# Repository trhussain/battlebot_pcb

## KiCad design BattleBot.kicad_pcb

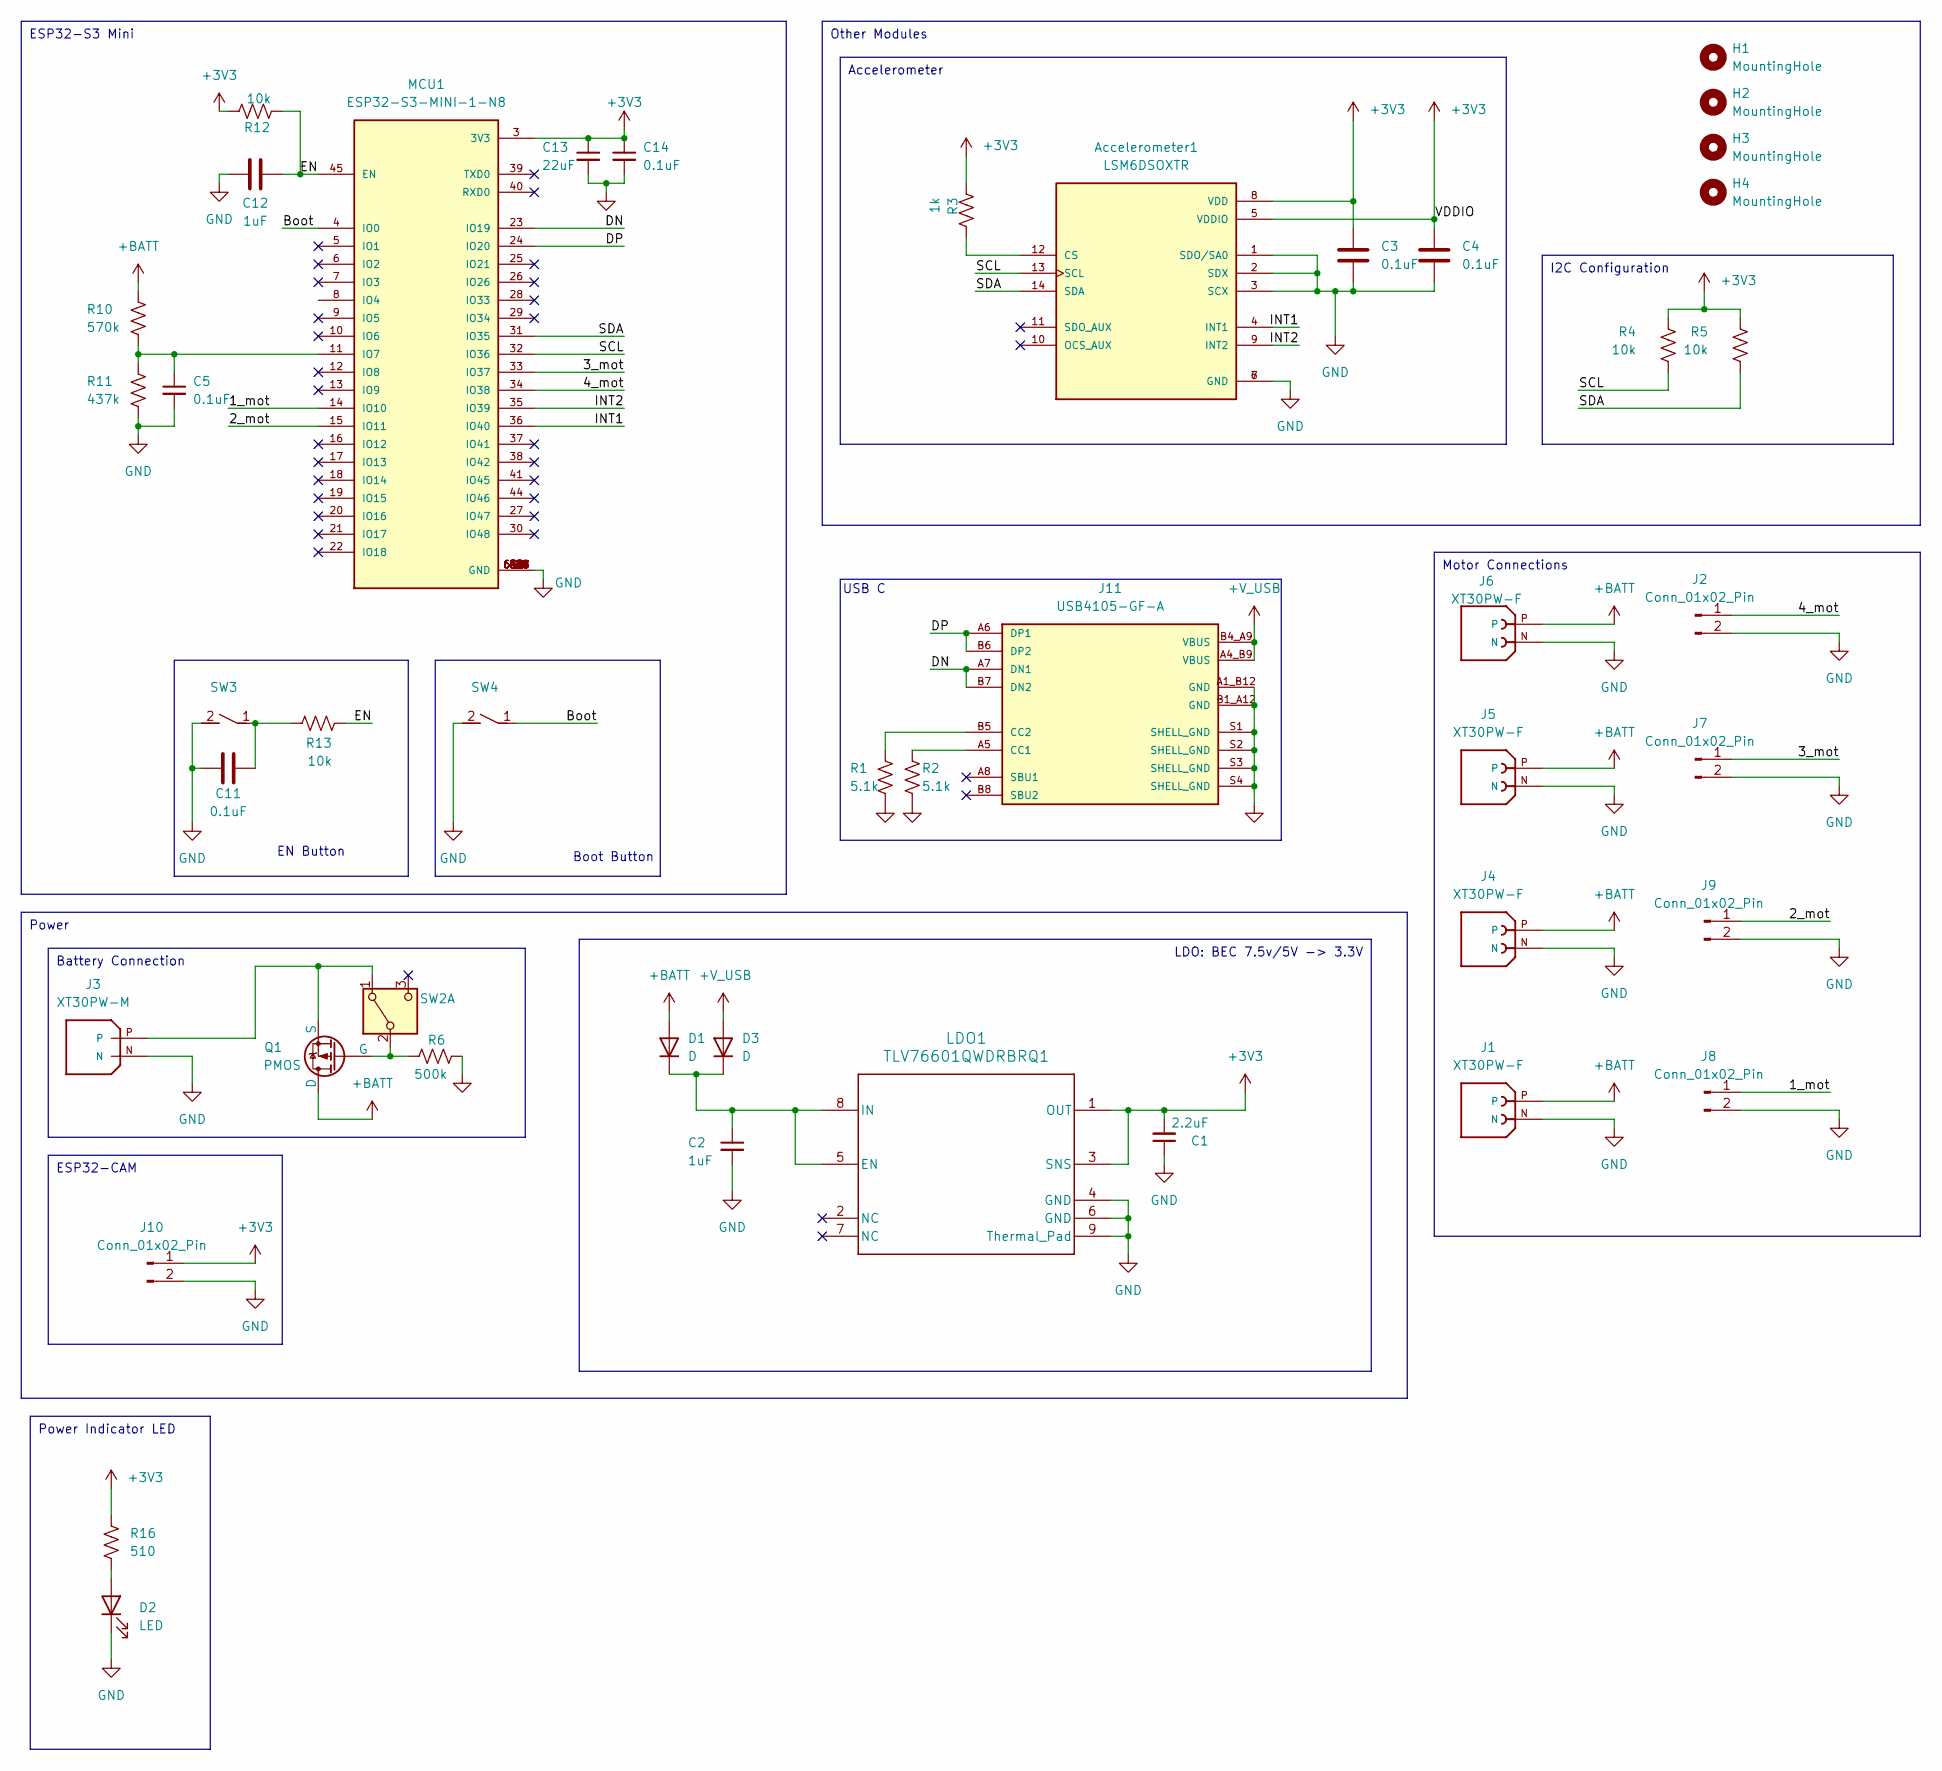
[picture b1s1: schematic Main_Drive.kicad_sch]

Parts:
Accelerometer1: LSM6DSOXTR; PQFN50P250X300X86-14N; PARTREV 3.0
C1: 2.2uF; C_0805_2012Metric
C2, C12: 1uF; C_0805_2012Metric
C3, C4, C5, C11, C14: 0.1uF; C_0805_2012Metric
C13: 22uF; C_0805_2012Metric
D1, D3: D; D_SOD-123F
D2: LED; LED_0603_1608Metric
H1, H2, H3, H4: MountingHole; MountingHole_3.2mm_M3_DIN965
J1, J4, J5, J6: XT30PW-F; AMASS_XT30PW-F; PARTREV 1.2
J2, J7, J8, J9, J10: Conn_01x02_Pin; PinHeader_1x02_P2.54mm_Horizontal
J3: XT30PW-M; AMASS_XT30PW-M; PARTREV 1.2
J11: USB4105-GF-A; GCT_USB4105-GF-A; PARTREV A3
LDO1: TLV76601QWDRBRQ1; DRB0008J-IPC_A
MCU1: ESP32-S3-MINI-1-N8; XCVR_ESP32-S3-MINI-1-N8; PARTREV v0.6
Q1: PMOS; PowerPAK_SO-8_Single
R1, R2: 5.1k; R_0805_2012Metric
R3: 1k; R_0805_2012Metric
R4, R5, R12, R13: 10k; R_0805_2012Metric
R6: 500k; R_0805_2012Metric
R10: 570k; R_0805_2012Metric
R11: 437k; R_0805_2012Metric
R16: 510; R_0805_2012Metric
SW2: SW_Nidec_CAS-120A1; SW_DPDT_CK_JS202011JCQN
SW3, SW4: rockerSwitch-434133025816

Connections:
+3V3: Accelerometer1.5 (VDDIO), Accelerometer1.8 (VDD), C1.2, C3.1, C4.1, C13.1, C14.1, J10.1, LDO1.1 (OUT), LDO1.3 (SNS), MCU1.3 (3V3), R3.2, R4.2, R5.2, R12.1, R16.1
+BATT: D1.2 (A), J1.P, J4.P, J5.P, J6.P, Q1.5 (D), R10.1
+V_USB: D3.2 (A), J11.A4_B9 (VBUS), J11.B4_A9 (VBUS)
/Main Drive /1_mot: J8.1, MCU1.14 (IO10)
/Main Drive /2_mot: J9.1, MCU1.15 (IO11)
/Main Drive /3_mot: J7.1, MCU1.33 (IO37)
/Main Drive /4_mot: J2.1, MCU1.34 (IO38)
/Main Drive /Boot: MCU1.4 (IO0), SW4.1
/Main Drive /DN: J11.A7 (DN1), J11.B7 (DN2), MCU1.23 (IO19)
/Main Drive /DP: J11.A6 (DP1), J11.B6 (DP2), MCU1.24 (IO20)
/Main Drive /EN: C12.2, MCU1.45 (EN), R12.2, R13.2
/Main Drive /INT1: Accelerometer1.4 (INT1), MCU1.36 (IO40)
/Main Drive /INT2: Accelerometer1.9 (INT2), MCU1.35 (IO39)
/Main Drive /SCL: Accelerometer1.13 (SCL), MCU1.32 (IO36), R4.1
/Main Drive /SDA: Accelerometer1.14 (SDA), MCU1.31 (IO35), R5.1
GND: Accelerometer1.1 (SDO/SA0), Accelerometer1.2 (SDX), Accelerometer1.3 (SCX), Accelerometer1.6 (GND), Accelerometer1.7 (GND), C1.1, C2.2, C3.2, C4.2, C5.2, C11.1, C12.1, C13.2, C14.2, D2.1 (K), J1.N, J2.2, J3.N, J4.N, J5.N, J6.N, J7.2, J8.2, J9.2, J10.2, J11.A1_B12 (GND), J11.B1_A12 (GND), J11.S1 (SHELL_GND), J11.S2 (SHELL_GND), J11.S3 (SHELL_GND), J11.S4 (SHELL_GND), LDO1.4 (GND), LDO1.6 (GND), LDO1.9 (Thermal_Pad), MCU1.1 (GND), MCU1.2 (GND), MCU1.42 (GND), MCU1.43 (GND), MCU1.46 (GND), MCU1.47 (GND), MCU1.48 (GND), MCU1.49 (GND), MCU1.50 (GND), MCU1.51 (GND), MCU1.52 (GND), MCU1.53 (GND), MCU1.54 (GND), MCU1.55 (GND), MCU1.56 (GND), MCU1.57 (GND), MCU1.58 (GND), MCU1.59 (GND), MCU1.60 (GND), MCU1.61 (GND), MCU1.61_1 (GND), MCU1.61_2 (GND), MCU1.61_3 (GND), MCU1.61_4 (GND), MCU1.61_5 (GND), MCU1.61_6 (GND), MCU1.61_7 (GND), MCU1.61_8 (GND), MCU1.62 (GND), MCU1.63 (GND), MCU1.64 (GND), MCU1.65 (GND), R1.2, R2.2, R6.2, R11.2, SW3.2, SW4.2
unnamed: Accelerometer1.12 (CS), R3.1
unnamed: C11.2, R13.1, SW3.1
unnamed: C2.1, D1.1 (K), D3.1 (K), LDO1.5 (EN), LDO1.8 (IN)
unnamed: D2.2 (A), R16.2
unnamed: J11.A5 (CC1), R2.1
unnamed: J11.B5 (CC2), R1.1
unnamed: C5.1, MCU1.11 (IO7), R10.2, R11.1
unnamed: Q1.4 (G), R6.1, SW2.2 (B)
unnamed: J3.P, Q1.1 (S), Q1.2 (S), Q1.3 (S), SW2.1 (A)

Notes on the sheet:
LDO: BEC 7.5v/5V -> 3.3V
Other Modules
ESP32-S3 Mini
Accelerometer
Power
I2C Configuration
Motor Connections
ESP32-CAM
Battery Connection
Power Indicator LED
USB C
Boot Button
EN Button

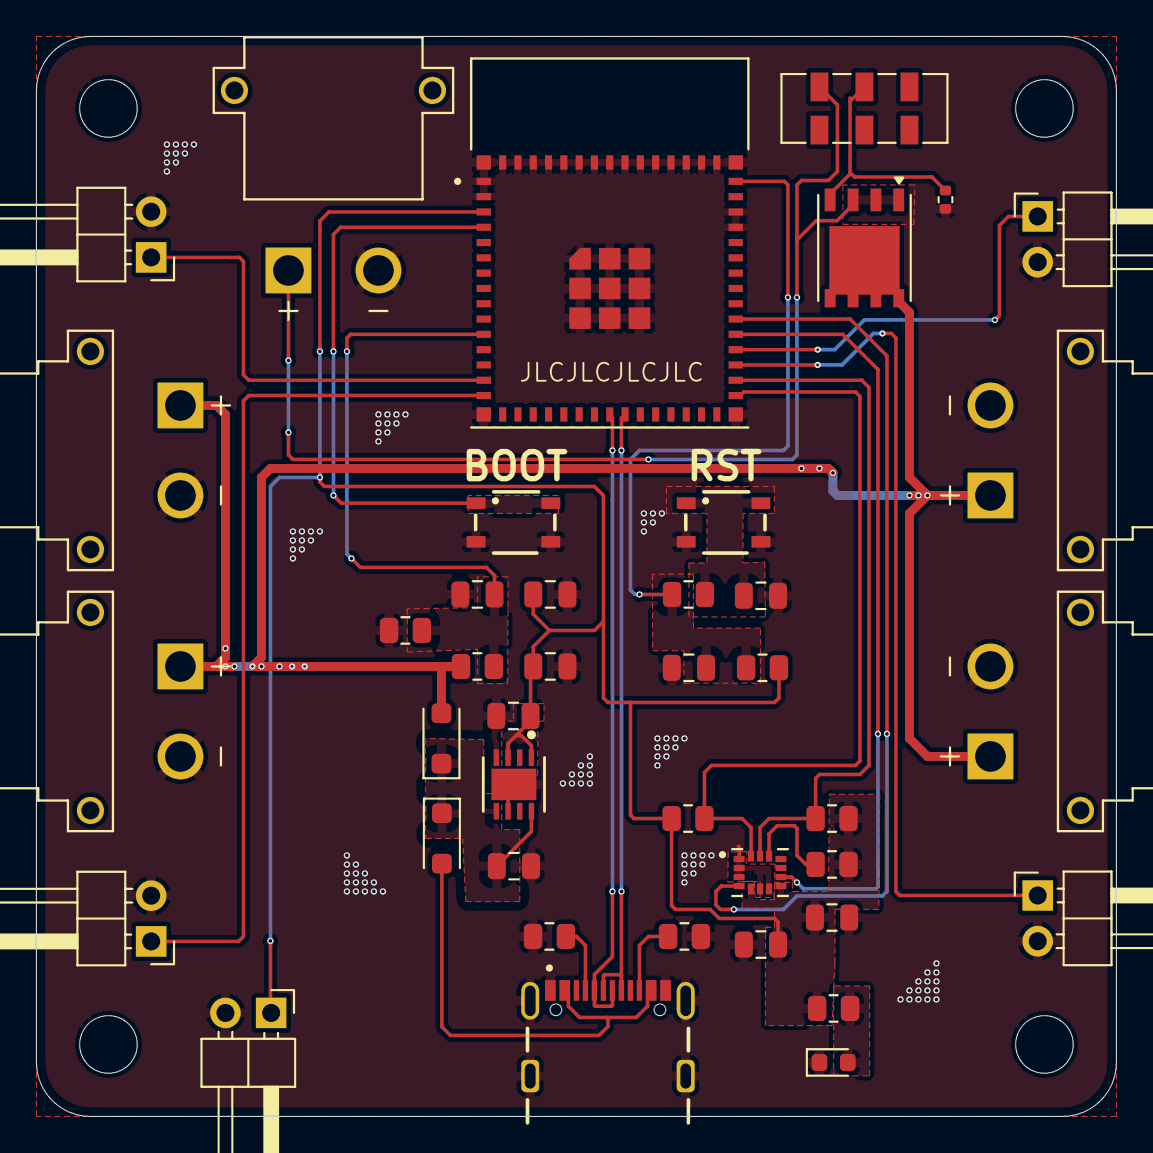
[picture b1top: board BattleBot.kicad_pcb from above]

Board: 2 copper layers, 60.0 x 60.0 mm, 45 parts (0 on the bottom side), 25 nets.

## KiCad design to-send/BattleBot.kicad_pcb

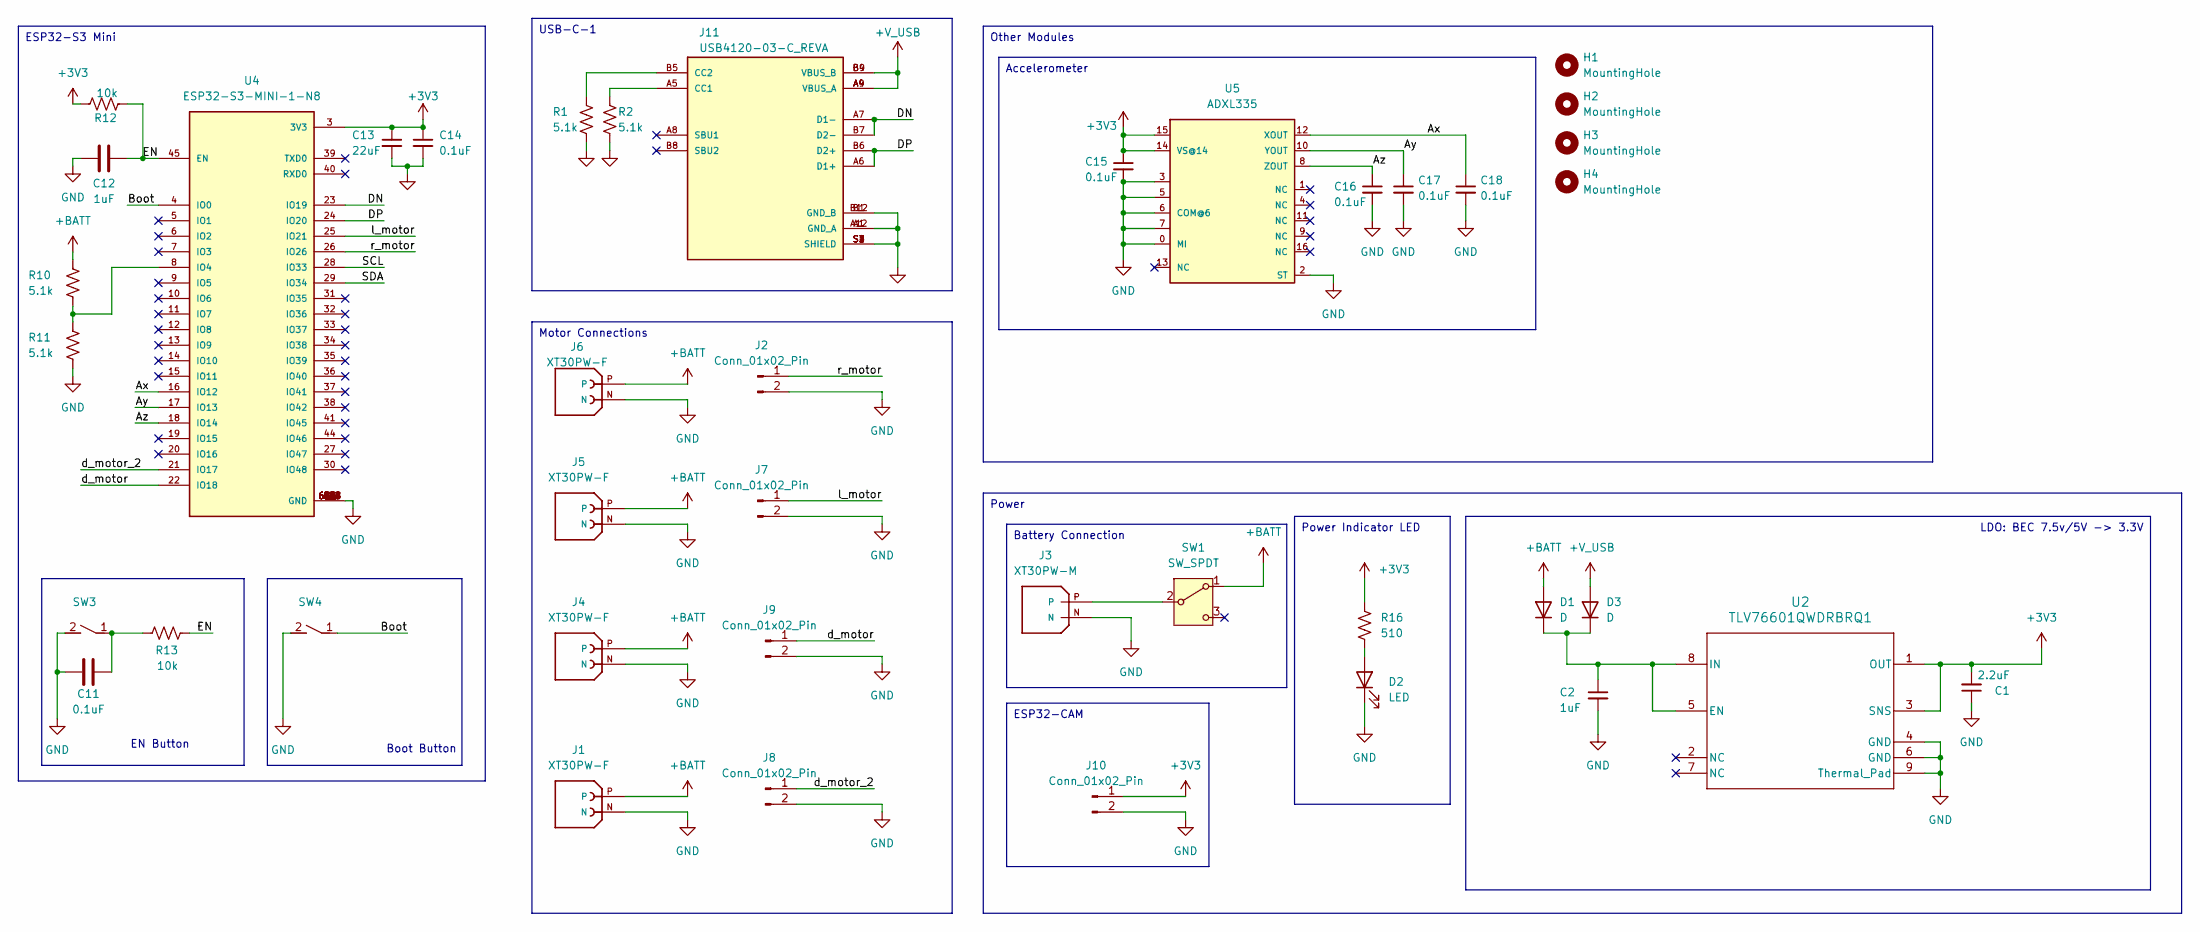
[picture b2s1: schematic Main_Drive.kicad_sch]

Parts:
C1: 2.2uF; C_0402_1005Metric
C2, C12: 1uF; C_0402_1005Metric
C11, C14, C15, C16, C17, C18: 0.1uF; C_0402_1005Metric
C13: 22uF; C_0402_1005Metric
D1, D3: D; D_SOD-123F
D2: LED; LED_0603_1608Metric
H1, H2, H3, H4: MountingHole; MountingHole_3.2mm_M3_DIN965
J1, J4, J5, J6: XT30PW-F; AMASS_XT30PW-F; PARTREV 1.2
J2, J7, J8, J9, J10: Conn_01x02_Pin; PinHeader_1x02_P2.54mm_Horizontal
J3: XT30PW-M; AMASS_XT30PW-M; PARTREV 1.2
J11: USB4120-03-C_REVA; GCT_USB4120-03-C_REVA; PARTREV A
R1, R2, R10, R11: 5.1k; R_0402_1005Metric
R12, R13: 10k; R_0402_1005Metric
R16: 510; R_0402_1005Metric
SW1: SW_SPDT; SW_JS102011JAQN
SW3, SW4: rockerSwitch-434133025816
U2: TLV76601QWDRBRQ1; DRB0008J-IPC_A
U4: ESP32-S3-MINI-1-N8; XCVR_ESP32-S3-MINI-1-N8; PARTREV v0.6
U5: ADXL335; LFCSP-16

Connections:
+3V3: C1.2, C13.1, C14.1, C15.1, J10.1, R12.1, R16.1, U2.1 (OUT), U2.3 (SNS), U4.3 (3V3), U5.14 (VS@14), U5.15
+BATT: D1.2 (A), J1.P, J4.P, J5.P, J6.P, R10.1, SW1.1 (A)
+V_USB: D3.2 (A), J11.A4 (VBUS_A), J11.A9 (VBUS_A), J11.B4 (VBUS_B), J11.B9 (VBUS_B)
/Main Drive /Ax: C18.1, U4.16 (IO12), U5.12 (XOUT)
/Main Drive /Ay: C17.1, U4.17 (IO13), U5.10 (YOUT)
/Main Drive /Az: C16.1, U4.18 (IO14), U5.8 (ZOUT)
/Main Drive /Boot: SW4.1, U4.4 (IO0)
/Main Drive /DN: J11.A7 (D1-), J11.B7 (D2-), U4.23 (IO19)
/Main Drive /DP: J11.A6 (D1+), J11.B6 (D2+), U4.24 (IO20)
/Main Drive /EN: C12.2, R12.2, R13.2, U4.45 (EN)
/Main Drive /SCL: U4.28 (IO33)
/Main Drive /SDA: U4.29 (IO34)
/Main Drive /d_motor: J9.1, U4.22 (IO18)
/Main Drive /d_motor_2: J8.1, U4.21 (IO17)
/Main Drive /l_motor: J7.1, U4.25 (IO21)
/Main Drive /r_motor: J2.1, U4.26 (IO26)
GND: C1.1, C2.2, C11.1, C12.1, C13.2, C14.2, C15.2, C16.2, C17.2, C18.2, D2.1 (K), J1.N, J2.2, J3.N, J4.N, J5.N, J6.N, J7.2, J8.2, J9.2, J10.2, J11.A1 (GND_A), J11.A12 (GND_A), J11.B1 (GND_B), J11.B12 (GND_B), J11.S1 (SHIELD), J11.S2 (SHIELD), J11.S3 (SHIELD), J11.S4 (SHIELD), R1.2, R2.2, R11.2, SW3.2, SW4.2, U2.4 (GND), U2.6 (GND), U2.9 (Thermal_Pad), U4.1 (GND), U4.2 (GND), U4.42 (GND), U4.43 (GND), U4.46 (GND), U4.47 (GND), U4.48 (GND), U4.49 (GND), U4.50 (GND), U4.51 (GND), U4.52 (GND), U4.53 (GND), U4.54 (GND), U4.55 (GND), U4.56 (GND), U4.57 (GND), U4.58 (GND), U4.59 (GND), U4.60 (GND), U4.61 (GND), U4.61_1 (GND), U4.61_2 (GND), U4.61_3 (GND), U4.61_4 (GND), U4.61_5 (GND), U4.61_6 (GND), U4.61_7 (GND), U4.61_8 (GND), U4.62 (GND), U4.63 (GND), U4.64 (GND), U4.65 (GND), U5.0 (MI), U5.2 (ST), U5.3, U5.5, U5.6 (COM@6), U5.7
unnamed: C11.2, R13.1, SW3.1
unnamed: C2.1, D1.1 (K), D3.1 (K), U2.5 (EN), U2.8 (IN)
unnamed: D2.2 (A), R16.2
unnamed: J11.A5 (CC1), R2.1
unnamed: J11.B5 (CC2), R1.1
unnamed: J3.P, SW1.2 (B)
unnamed: R10.2, R11.1, U4.8 (IO4)

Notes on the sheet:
LDO: BEC 7.5v/5V -> 3.3V
USB-C-1
Other Modules
ESP32-S3 Mini
Accelerometer
Power
Motor Connections
ESP32-CAM
Battery Connection
Power Indicator LED
Boot Button
EN Button

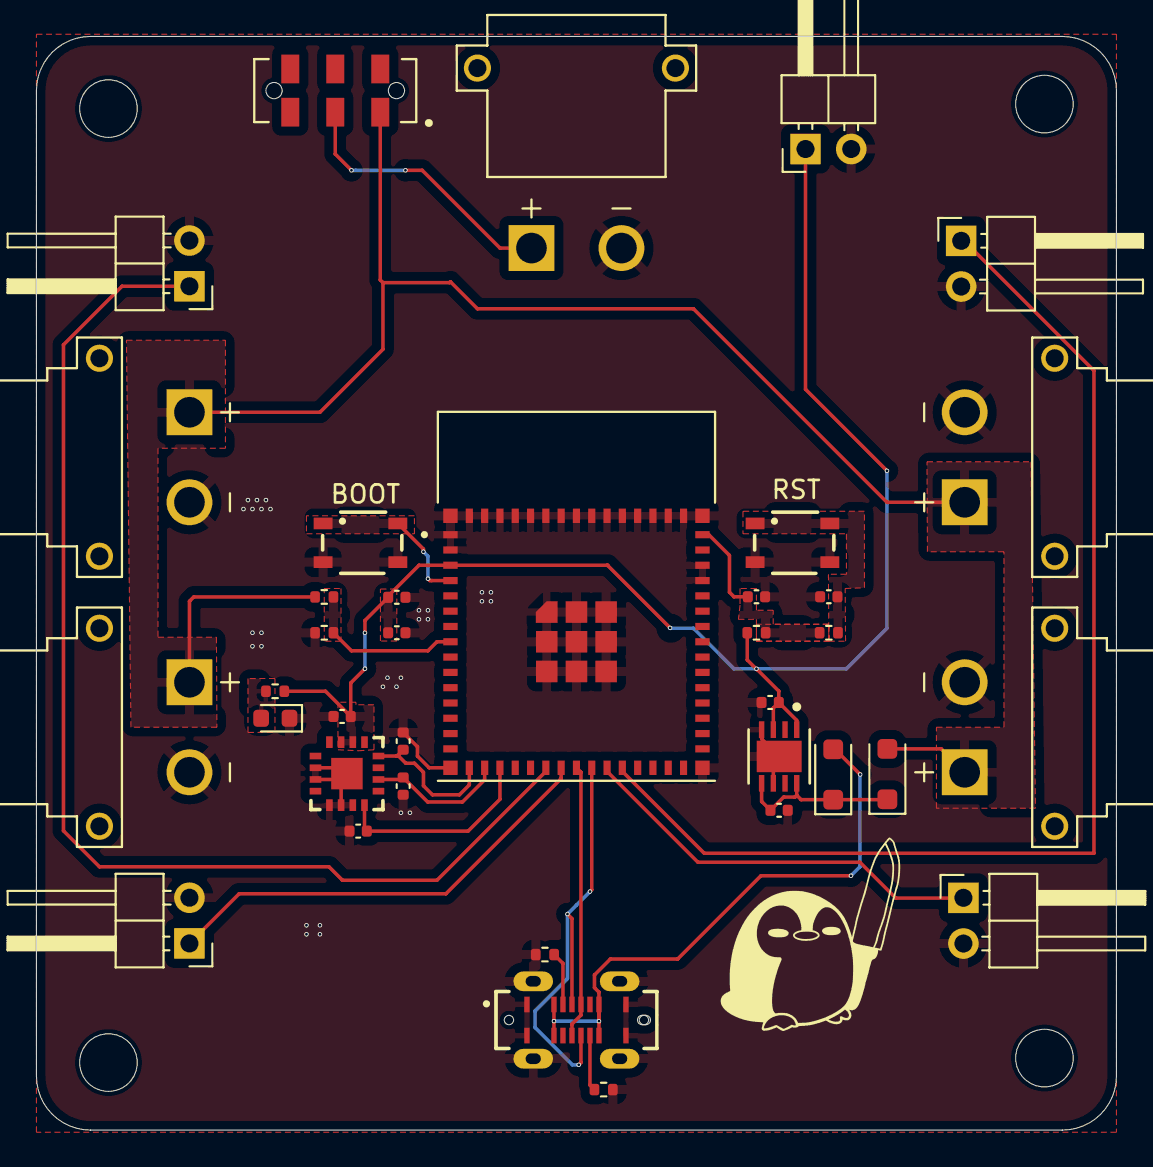
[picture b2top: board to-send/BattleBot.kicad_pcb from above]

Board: 2 copper layers, 60.0 x 60.8 mm, 41 parts (0 on the bottom side), 22 nets.

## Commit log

2024-09-19 Before changing everything to 0805 components
    ---------
    N/A
    In Progress
    ---------
    N/A
    Errors
2024-09-29 Newly updated version, should be ready for ordering, ask Colin tomorrow
2024-09-30 9/29 Ordered PCB
2024-09-30 OKAY THIS ONE IS THE ORDERED ONE
